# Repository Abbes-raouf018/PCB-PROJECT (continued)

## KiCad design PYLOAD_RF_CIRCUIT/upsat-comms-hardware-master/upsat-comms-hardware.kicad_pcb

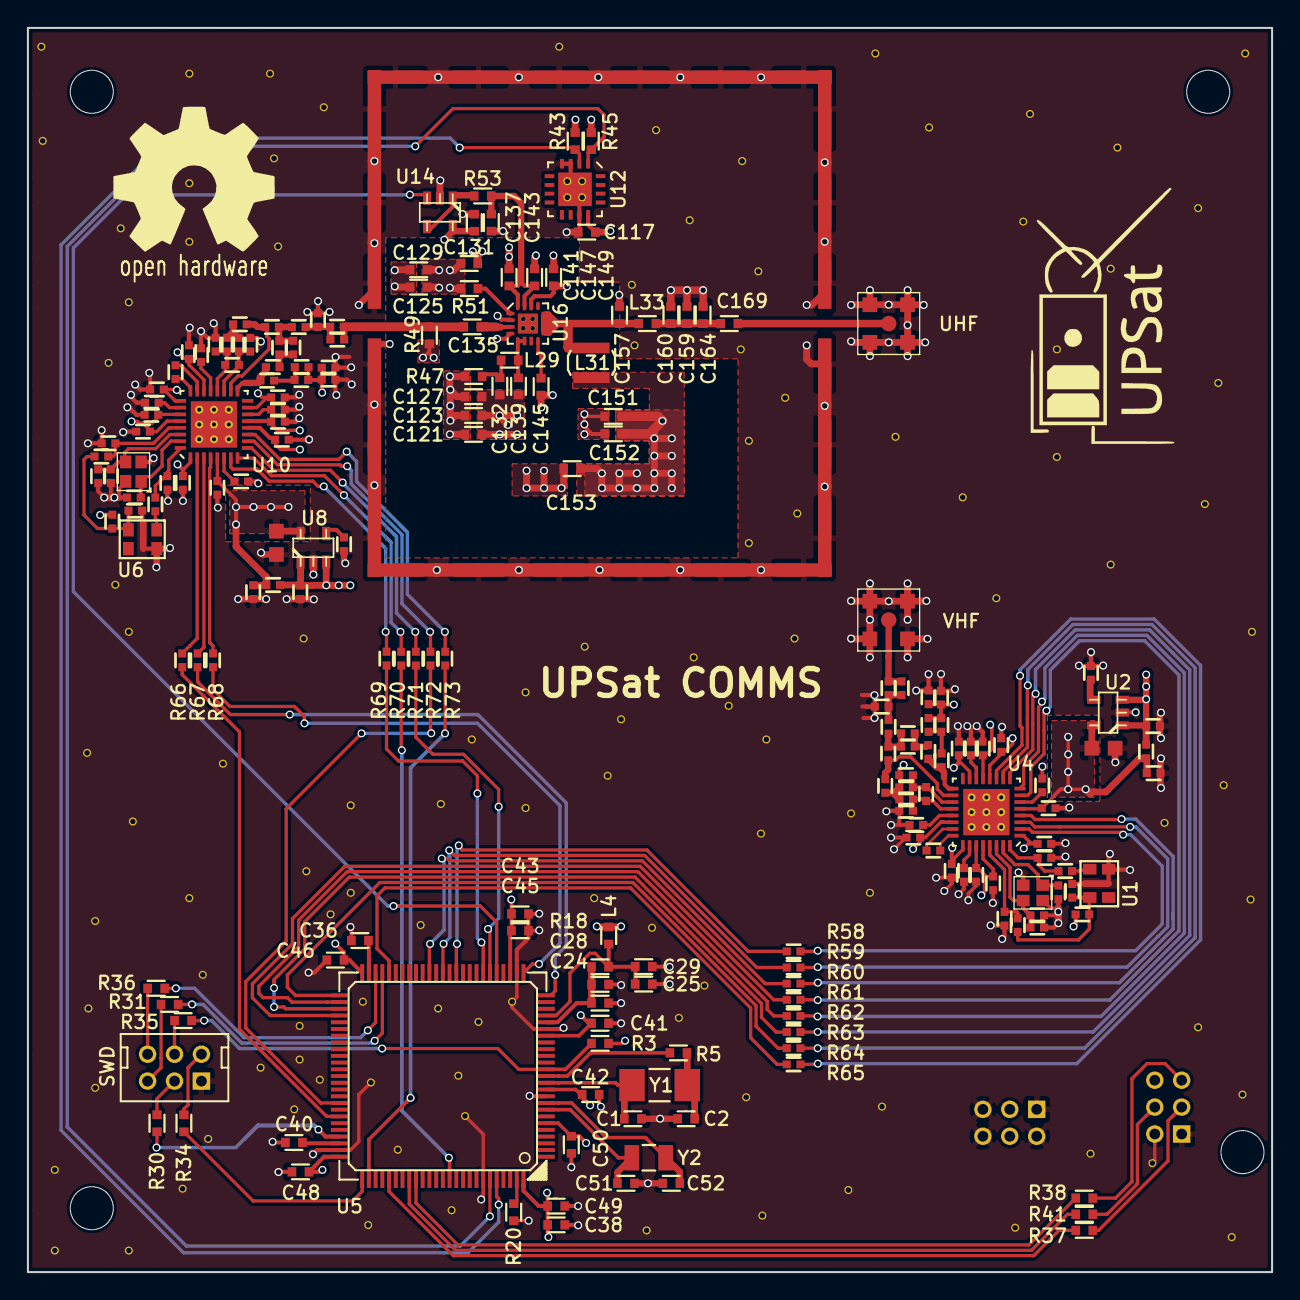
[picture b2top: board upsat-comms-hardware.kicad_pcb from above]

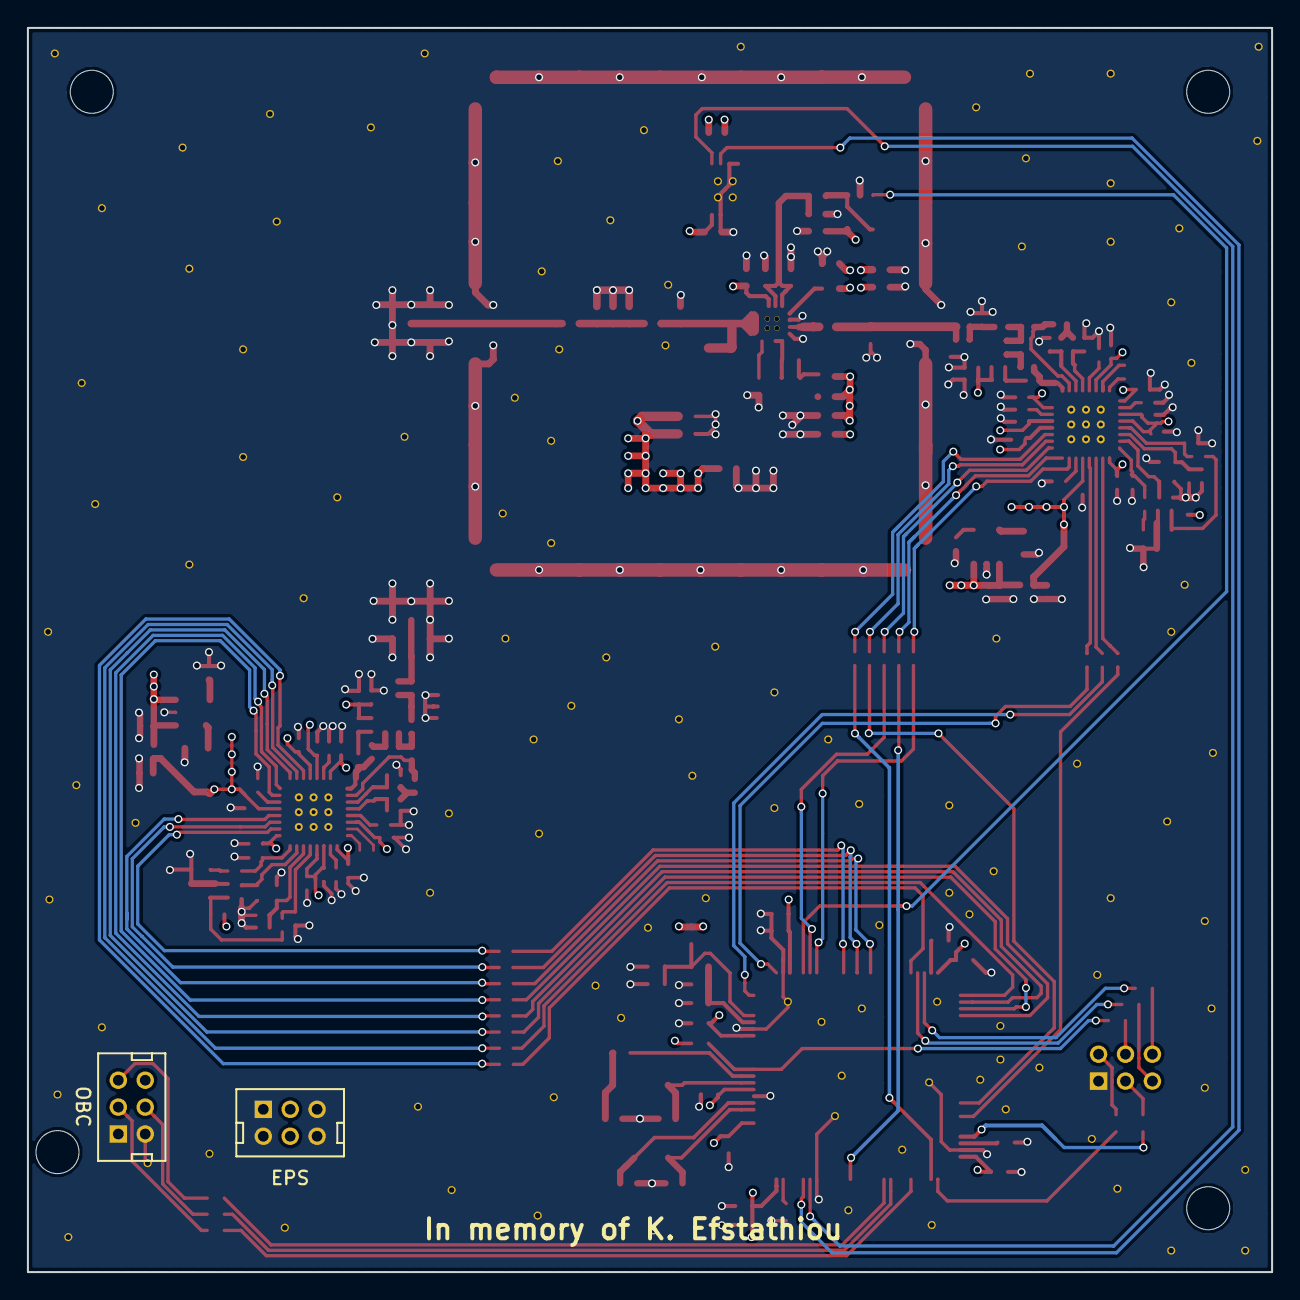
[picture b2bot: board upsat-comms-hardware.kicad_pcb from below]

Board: 4 copper layers, 92.5 x 92.5 mm, 195 parts (2 on the bottom side), 120 nets.

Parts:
C1, C2: 20pF; 0603murata2
C3, C4, C53, C55: 100nF; 0402_cc
C5, C6, C12, C13, C15, C16, C18, C19, C21, C22, C23, C26, C57, C58, C71, C73, C77, C79, C83, C85, C89, C91, C93, C95: 47nF; 0402_cc
C7, C61: 220nF; 0402_cc
C8, C27, C30, C62, C96, C99: 10nF; 0402_cc
C9, C65: 22pF; 0402_cc
C10, C11, C67, C69: 15pF; 0402_cc
C14, C75: TBD; 0402_cc
C17, C81: 2.2uF; CC1120DecCAP
C20, C87: 1.8nF; 0402_cc
C24, C25, C38, C41, C42, C43, C45, C46, C48, C49, C137: 100nF; 0603murata2
C28, C29, C50: 1uF; 0603murata2
C31: 150 pF; 0402_cc
C32: 100 pF; 0402_cc
C33, C105: 100pF; 0402_cc
C34, C35, C37, C39: 15 pF; 0402_cc
C36, C40: 2.2uF; 0603murata2
C44: 18 pF; 0402_cc
C47: 1.8 pF; 0402_cc
C51, C52: 6.8pF; 0603murata2
C101: 39pF; 0402_cc
C103: 56pF; 0402_cc
C107: 2.2pF; 0402_cc
C109, C111, C113: 5.1pF; 0402_cc
C115: 6.2pF; 0402_cc
C117: 0.1uF; 0603murata2
C118: do not mount; 0402_cc
C121, C153: 3.3uF; 0603murata2
C123, C125, C141, C147: 10000pF; 0603murata2
C127, C129, C143, C152: 1nF; 0603murata2
C131, C132: 330pF; 0603murata2
C135, C169: 56pF; 0603murata2
C139, C145: 18pF; 0603murata2
C149, C151: 47pF; 0603murata2
C157: TBD; 0603murata2
C159: 6.8 pF; 0603murata2
C160: 22 pF; 0603murata2
C164: 4 pF; 0603murata2
EPS: CONN_02X03; hrs-df11-6dp-2dsa
L1, L11: BLM15HG102SN1D; 0402_cc
L2: 150 nH; 0402_cc
L3: 180 nH; 0402_cc
L4: fcm1608-0603; 0603murata2
L5: 19 nH; 0402_cc
L6, L7: 91 nH; 0402_cc
L8: 120 nH; 0402_cc
L9: 43 nH; 0402_cc
L10: 75 nH; 0402_cc
L13, L15: 56nH; 0402_cc
L17, L25: 15nH; 0402_cc
L19, L21: 27nH; 0402_cc
L23: 43nH; 0402_cc
L27: 22nH; 0402_cc
L29: 6.8nH; 0603murata2
L31: Taiyo Yuden; Taiyo_Yuden_bead
L33: 4.3 nH; 0603murata2
OBC: OBC; hrs-df11-6dp-2dsa
R3, R43, R45: 10K; 0603murata2
R5: 220; 0603murata2
R8, R9, R10, R24, R26, R27, R58, R59, R60, R61, R62, R63, R64, R65, R66, R67, R68, R69, R70, R71, R72, R73: 0; 0402_cc
R17, R32: 56K; 0402_cc
R18: 47; 0603murata2
R19: 22 Ohm; 0402_cc
R20, R47: 0; 0603murata2
R30, R31, R34, R35, R36, R37, R38, R41: 470; 0603murata2
R39: 18; 0402_cc
R49: 180; 0603murata2
R51: 18; 0603murata2
R53: 180 Ohm; 0603murata2
RFSHIELD1: TEST_1P; BMI-S-x06
SWD: SWD; hrs-df11-6dp-2dsa
U1, U6: TXCO_TG_5021CG; TXCOTG5021CG
U2, U8: TPS79930; sot23-5
U3, U18: FA_128_; crystal_fa128
U4, U10: CC1120; cc1120
U5: STM32F407VG; TQFP-100
U12: ADT7420
U14: OPA320; sot23-5
U16: RF5110G
UHF: SMA; mmcx_conn
VHF: SMA; mmcx_conn
Y1: Crystal; ABM3crystal
Y2: Crystal; ABS07crystal

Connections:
+3V3: C4.1, C38.1, C41.1, C42.1, C43.1, C45.1, C46.1, C48.1, C49.1, C50.1, C55.1, C117.1, C121.1, C123.1, C125.1, C127.1, C129.1, C131.1, C137.1, C149.1, C151.2, C152.2, C153.2, EPS.3, EPS.4, L1.2, L4.2, L11.2, L31.2, R3.2, R43.1, R45.1, R47.1, R51.1, U2.1, U2.3, U5.6, U5.11, U5.19, U5.28, U5.50, U5.75, U5.100, U8.1, U8.3, U12.12, U14.5, U16.14
/1CS_N: R73.1, U5.77
/1GPIO0: R72.1, U5.67
/1GPIO2: R68.1, U5.26
/1GPIO3: R67.1, U5.25
/1RESET_N: R66.1, U5.69
/2CS_N: R65.1, U5.46
/2GPIO0: R64.1, U5.51
/2GPIO2: R60.1, U5.40
/2GPIO3: R59.1, U5.38
/2RESET_N: R58.1, U5.36
/COMMS_TO_OBC_EN: R38.2, U5.84
/COMMS_TO_OBC_RX: R41.1, U5.83
/COMMS_TO_OBC_TX: R37.2, U5.80
/DAC_OUT2: U5.30, U14.3
/I2C1_SCL: R45.2, U5.95, U12.1
/I2C1_SDA: R43.2, U5.96, U12.2
/NRST: R3.1, R35.1, U5.14
/SPI1_MISO: R71.1, U5.31
/SPI1_MOSI: R69.1, U5.32
/SPI1_SCK: R70.1, U5.89
/SPI2_MISO: R63.1, U5.53
/SPI2_MOSI: R61.1, U5.54
/SPI2_SCK: R62.1, U5.52
/SWCLK: R34.1, U5.76
/SWDIO: R30.2, U5.72
/USART3_RX: R36.1, U5.48
/USART3_TX: R31.2, U5.47
GND: C1.1, C2.1, C3.2, C4.2, C5.2, C6.2, C7.2, C8.2, C10.1, C11.1, C12.1, C13.2, C14.1, C15.2, C16.1, C17.2, C18.2, C19.1, C21.1, C22.2, C23.1, C24.2, C25.1, C26.1, C27.1, C28.2, C29.1, C30.2, C33.2, C35.1, C36.2, C38.2, C40.2, C41.2, C42.2, C43.2, C44.2, C45.2, C46.2, C48.2, C49.2, C50.2, C51.1, C52.1, C53.2, C55.2, C57.2, C58.2, C61.2, C62.2, C67.1, C69.1, C71.1, C73.2, C75.1, C77.2, C79.1, C81.2, C83.2, C85.1, C89.1, C91.2, C93.1, C95.1, C96.1, C99.2, C105.2, C109.1, C115.2, C117.2, C121.2, C123.2, C125.2, C127.2, C129.2, C131.2, C132.2, C137.2, C139.2, C141.2, C143.2, C145.2, C147.2, C149.2, C151.1, C152.1, C153.1, C157.1, C159.1, C160.2, C164.2, EPS.1, EPS.2, EPS.5, EPS.6, L7.1, L21.1, OBC.1, OBC.2, R10.1, R17.2, R20.2, R27.1, R32.2, R49.2, RFSHIELD1.1, SWD.1, U1.2, U2.2, U3.2, U3.4, U4.33, U5.10, U5.20, U5.27, U5.74, U5.94, U6.2, U8.2, U10.33, U12.3, U12.4, U12.11, U12.17, U14.2, U16.2, U16.4, U16.17, U18.2, U18.4, UHF.2, UHF.3, UHF.4, UHF.5, VHF.2, VHF.3, VHF.4, VHF.5
unnamed: C1.2, U5.12, Y1.1
unnamed: C2.2, R5.2, Y1.2
unnamed: C3.1, R8.2, R9.1, U1.4
unnamed: C7.1, U4.6
unnamed: C8.1, U2.4
unnamed: C9.1, R10.2, U4.32
unnamed: C9.2, U1.3
unnamed: C10.2, U3.1, U4.31
unnamed: C11.2, C14.2, U3.3, U4.30
unnamed: C12.2, R9.2, U4.29
unnamed: C20.1, U4.23
unnamed: C20.2, U4.24
unnamed: C21.2, U4.26
unnamed: C24.1, C28.1, R18.1, U5.21
unnamed: C25.2, C29.2, L4.1, R18.2, U5.22
unnamed: C27.2, U4.21
unnamed: C31.1, C34.2, L5.2
unnamed: C31.2, L2.1, U4.17
unnamed: C32.1, L2.2, R19.1
unnamed: C34.1, C39.2, L5.1, L8.2
unnamed: C35.2, L3.1, L6.2, U4.20
unnamed: C36.1, U5.49
unnamed: C37.1, L6.1, L9.1
unnamed: C37.2, L3.2, L7.2, U4.19
unnamed: C39.1, L9.2, U4.18
unnamed: C40.1, U5.73
unnamed: C44.1, C47.2, L8.1, L10.2
unnamed: C47.1, L10.1, VHF.1
unnamed: C51.2, U5.8, Y2.1
unnamed: C52.2, U5.9, Y2.2
unnamed: C53.1, R24.2, R26.1, U6.4
unnamed: C61.1, U10.6
unnamed: C62.1, U8.4
unnamed: C65.1, R27.2, U10.32
unnamed: C65.2, U6.3
unnamed: C67.2, U10.31, U18.1
unnamed: C69.2, C75.2, U10.30, U18.3
unnamed: C71.2, R26.2, U10.29
unnamed: C87.1, U10.23
unnamed: C87.2, U10.24
unnamed: C89.2, U10.26
unnamed: C96.2, U10.21
unnamed: C101.1, C107.2, L17.2
unnamed: C101.2, L13.1, U10.17
unnamed: C103.1, L13.2, R39.1
unnamed: C107.1, C113.2, L17.1, L23.2
unnamed: C109.2, L15.1, L19.2, U10.20
unnamed: C111.1, L19.1, L25.1
unnamed: C111.2, L15.2, L21.2, U10.19
unnamed: C113.1, L25.2, U10.18
unnamed: C115.1, C118.2, L23.1, L27.2
unnamed: C118.1, C135.2, L27.1, R49.1
unnamed: C132.1, L29.2, R47.2
unnamed: C135.1, U16.3
unnamed: C139.1, L29.1, U16.5, U16.6
unnamed: C141.1, C143.1, C147.1, R53.2, U16.15, U16.16
unnamed: C145.1, U16.8
unnamed: C157.2, L31.1, L33.2, U16.9, U16.10, U16.11, U16.12
unnamed: C159.2, C160.1, C164.1, C169.2, L33.1
unnamed: C169.1, UHF.1
unnamed: R34.2, SWD.2
unnamed: R30.1, SWD.3
unnamed: R35.2, SWD.4
unnamed: R31.1, SWD.5
unnamed: R36.2, SWD.6
unnamed: OBC.3, R37.1
unnamed: OBC.4, R41.2
unnamed: OBC.5, R38.1
unnamed: R5.1, U5.13
unnamed: R17.1, U4.14
unnamed: R20.1, U5.99
unnamed: R32.1, U10.14
unnamed: R51.2, U16.1
unnamed: R53.1, U14.1, U14.4
unnamed: R58.2, U4.2
unnamed: R59.2, U4.3
unnamed: R60.2, U4.4
unnamed: R61.2, U4.7
unnamed: R62.2, U4.8
unnamed: R63.2, U4.9
unnamed: R64.2, U4.10
unnamed: R65.2, U4.11
unnamed: R66.2, U10.2
unnamed: R67.2, U10.3
unnamed: R68.2, U10.4
unnamed: R69.2, U10.7
unnamed: R70.2, U10.8
unnamed: R71.2, U10.9
unnamed: R72.2, U10.10
unnamed: R73.2, U10.11
VDD: C5.1, C6.1, C13.1, C15.1, C16.2, C17.1, C18.1, C19.2, C22.1, C23.2, C26.2, C30.1, C32.2, C33.1, C57.1, C58.1, C73.1, C77.1, C79.2, C81.1, C83.1, C85.2, C91.1, C93.2, C95.2, C99.1, C103.2, C105.1, L1.1, L11.1, R8.1, R19.2, R24.1, R39.2, U2.5, U4.1, U4.5, U4.12, U4.13, U4.15, U4.22, U4.25, U4.27, U4.28, U8.5, U10.1, U10.5, U10.12, U10.13, U10.15, U10.22, U10.25, U10.27, U10.28

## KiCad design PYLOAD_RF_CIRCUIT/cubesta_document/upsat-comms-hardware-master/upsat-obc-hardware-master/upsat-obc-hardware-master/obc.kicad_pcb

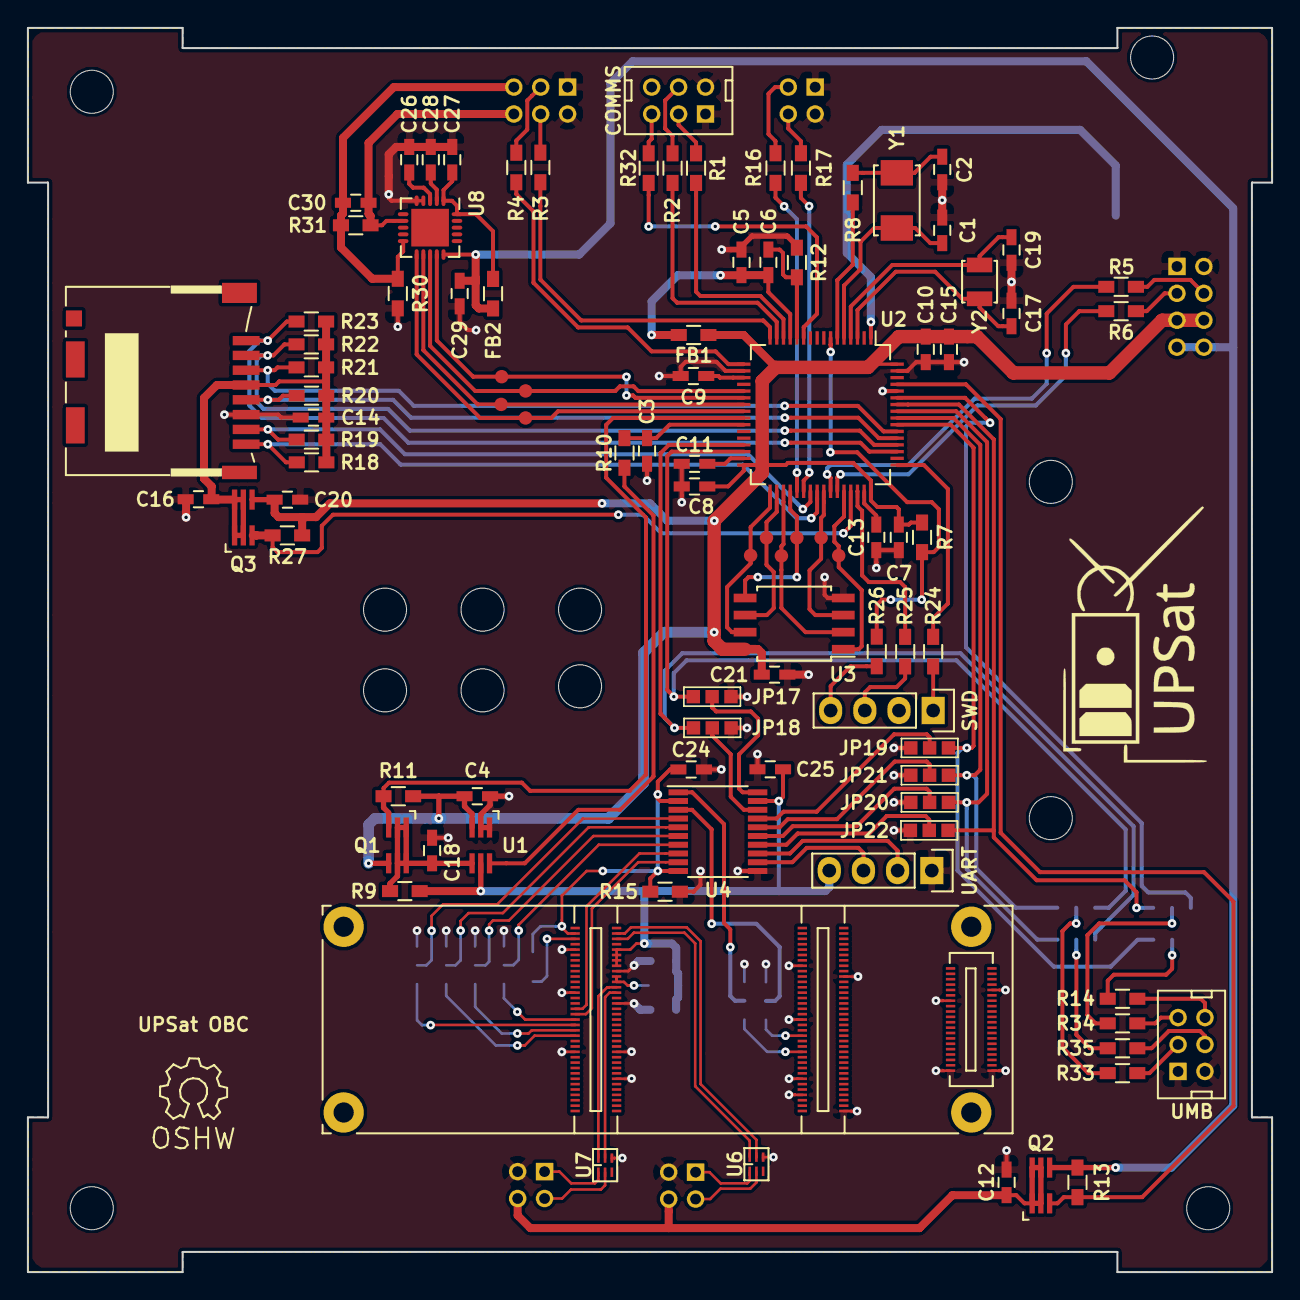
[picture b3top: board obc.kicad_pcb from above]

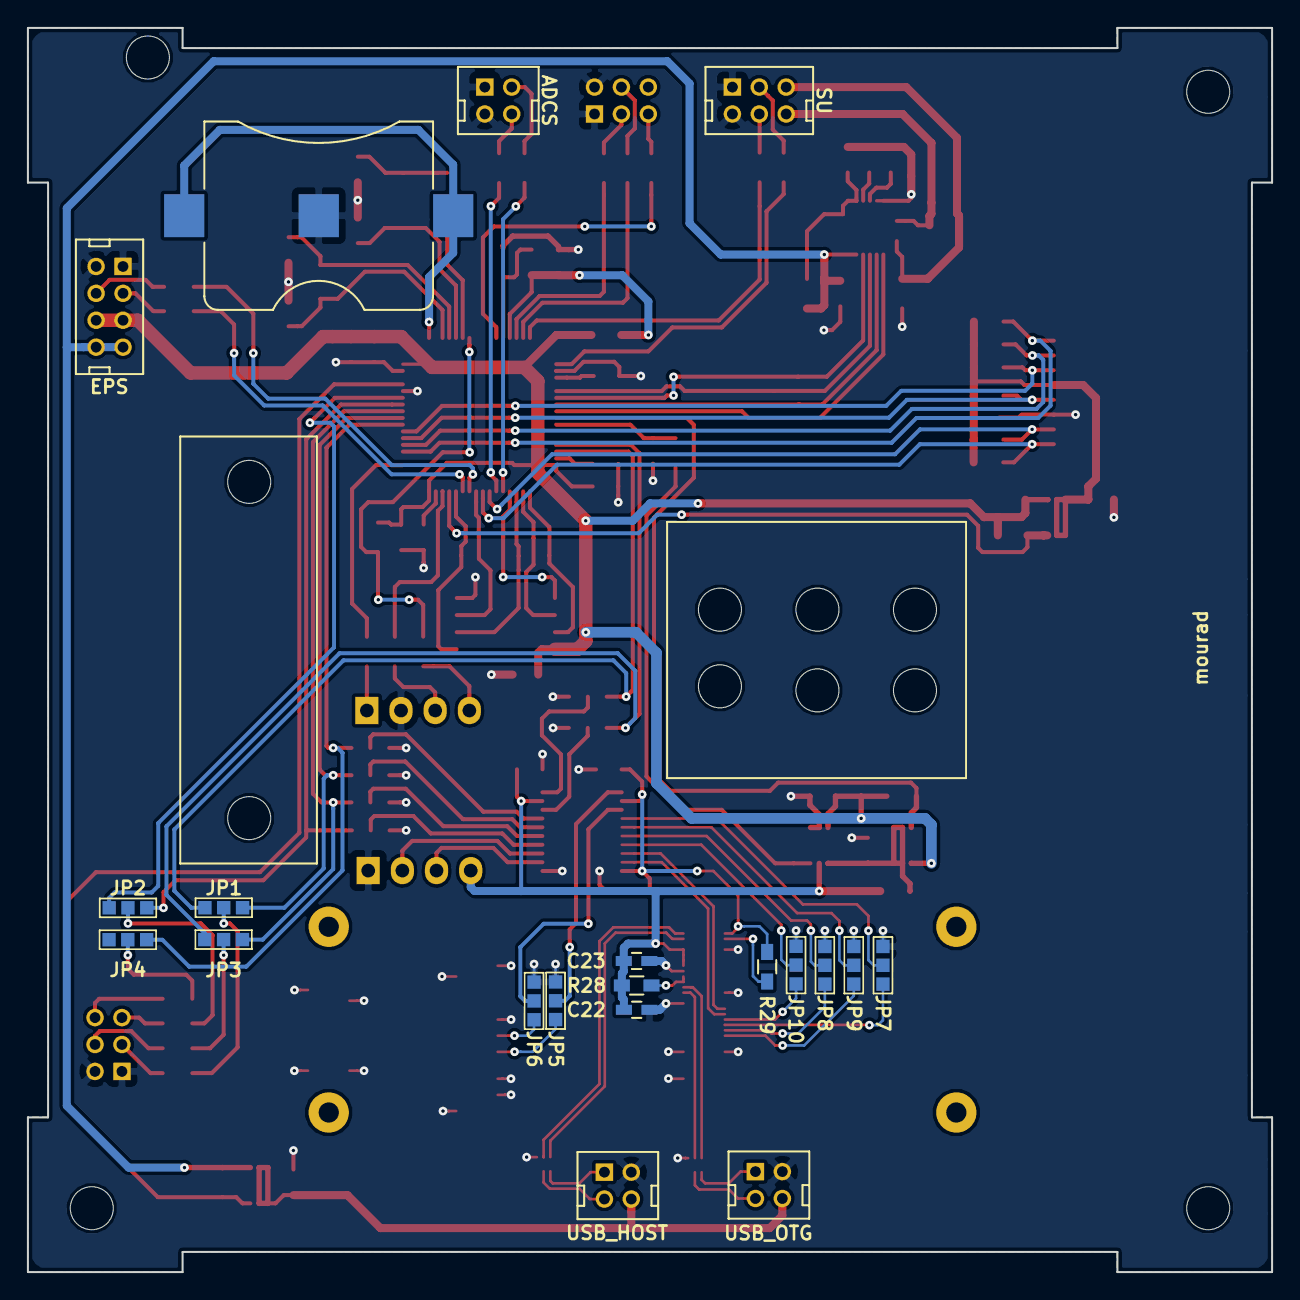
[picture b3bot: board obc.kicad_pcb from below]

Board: 2 copper layers, 92.5 x 92.5 mm, 119 parts (21 on the bottom side), 116 nets.

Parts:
BT1: Battery; renata-smtm1632
C1, C2: 20p; C_0603_HandSoldering
C3, C4, C7, C9, C10, C14, C20, C24, C25, C26, C30: 100n; C_0603_HandSoldering
C5, C11, C13, C27, C29: 2.2u; C_0603_HandSoldering
C6: 10n; C_0603_HandSoldering
C8, C12, C15, C16, C18, C21, C28: 10u; C_0603_HandSoldering
C17, C19: 6.8p; C_0603_HandSoldering
C22, C23: 22u; C_0603_HandSoldering
CAMERA1: upsat_camera
CON1: hrs-dm3cs
FB1, FB2: BLM18AG331SN1; R_0603_HandSoldering
JP1, JP2, JP3, JP4, JP5, JP6, JP7, JP8, JP9, JP10, JP17, JP18, JP19, JP20, JP21, JP22: JUMPER3; 3-way_bridge_0603
P1: EPS; hrs-df11-8dp-2dsa
P2: COMMS; hrs-df11-6dp-2dsa
P3: ADCS; hrs-df11-4dp-2dsa
P4: SU; hrs-df11-6dp-2dsa
P5: UMB; hrs-df11-6dp-2dsa
P6: SWD; Pin_Header_Straight_1x04
P7: UART; Pin_Header_Straight_1x04
P8: USB_HOST; hrs-df11-4dp-2dsa
P9: USB_OTG; hrs-df11-4dp-2dsa
Q1, Q2, Q3: Si1401EDH; SC-70-6_Handsoldering
R1, R2, R3, R4, R5, R6, R10, R14, R16, R17, R24, R25, R26, R32, R33, R34, R35: 470; R_0603_HandSoldering
R7: 10k; R_0603_HandSoldering
R8: 220; R_0603_HandSoldering
R9: 0.02; R_0603_HandSoldering
R11, R13, R27, R29: 100k; R_0603_HandSoldering
R12, R30: 0; R_0603_HandSoldering
R15, R28: 1k; R_0603_HandSoldering
R18, R19, R20, R21, R22, R23: 47k; R_0603_HandSoldering
R31: 2.4k; R_0603_HandSoldering
U1: INA214; SC-70-6_Handsoldering
U2: STM32F405R; LQFP-64_10x10mm_Pitch0.5mm
U3: IS25LP128; SOIJ-8_5.3x5.3mm_Pitch1.27mm
U4: TXB0108PWR; TSSOP-20_4.4x6.5mm_Pitch0.65mm
U5: DART-4460; dart-4460
U6, U7: ECMF02-3HSM6
U8: AD7689; UQFN-20-1EP_4x4mm_Pitch0.5mm
UPSat OBC: Symbol_OSHW-Logo_SilkScreen
W1, W2, W3, W4, W5, W6, W7, W8, W9, W10: TEST_1P; Measurement_Point_Round-SMD-Pad_Small
Y1: 12MHz; ABM3
Y2: 32.768kHz; ABS07crystal

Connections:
+3V3: C4.2, C7.1, C8.1, C10.1, C15.2, C20.1, C21.1, FB1.1, P1.5, P1.6, Q1.4, Q3.4, R7.2, R11.2, R27.2, U1.3, U2.32, U2.48, U2.64, U3.8
+5V: C29.1, FB2.2, P1.7, P1.8, Q2.4, R13.2, U8.15
/ADCS_RX: P3.4, R17.1
/ADCS_TX: P3.3, R16.1
/COMMS_EN: P2.5, R32.1
/COMMS_RX: P2.4, R2.1
/COMMS_TX: P2.3, R1.1
/EPS_RX: P1.3, R6.2
/EPS_TX: P1.4, R5.2
/F_CE: U2.44, U3.1, W3.1
/F_HOLD: U2.33, U3.7, W4.1
/F_MISO: U2.35, U3.2, W2.1
/F_MOSI: U2.36, U3.5, W6.1
/F_SCK: U2.34, U3.6, W5.1
/F_WP: U2.41, U3.3, W1.1
/IAC/+3.3V: C22.1, C23.1, C25.1, P7.4, R9.1, R28.2, U1.5, U4.19, U5.10, U5.12, U5.14, U5.16
/IAC/+5V: C12.2, P8.4, P9.4, Q2.1, Q2.2, Q2.5, Q2.6
/IAC/A1: JP5.2, U4.1
/IAC/A2: JP6.2, U4.3
/IAC/A5: JP7.2, U4.4
/IAC/A6: JP9.2, U4.5
/IAC/A7: JP8.2, U4.6
/IAC/A8: JP10.2, U4.7
/IAC/B1: JP17.2, U4.20
/IAC/B2: JP18.2, U4.18
/IAC/B5: JP19.2, U4.17
/IAC/B6: JP21.2, U4.16
/IAC/B7: JP20.2, U4.15
/IAC/B8: JP22.2, U4.14
/IAC/DART_CLK: JP7.1, U5.37
/IAC/DART_CS: JP10.1, U5.35
/IAC/DART_MISO: JP9.1, U5.41
/IAC/DART_MOSI: JP8.1, U5.39
/IAC/Dcon+: P8.1, U6.1
/IAC/Dcon-: P8.2, U6.2
/IAC/RX: JP3.3, JP18.3, U2.29
/IAC/RX1: JP6.1, U5.111
/IAC/RX3: U4.8, U5.31
/IAC/RX_UART: P7.2, U4.13
/IAC/TX: JP1.1, JP17.3, U2.30
/IAC/TX1: JP5.1, U5.117
/IAC/TX3: U4.9, U5.33
/IAC/TX_UART: P7.3, U4.12
/IAC/USB_HOST_D+: U5.6, U6.6
/IAC/USB_HOST_D-: U5.4, U6.5
/IAC/USB_OTG_D+: U5.24, U7.6
/IAC/USB_OTG_D-: U5.26, U7.5
/IAC/VIO: C24.1, R15.1, R29.1, U4.2, U4.10, U5.3
/IAC/uC_CS: JP2.1, JP22.3, U2.58
/IAC/uC_MISO: JP1.3, JP21.3, U2.56
/IAC/uC_MOSI: JP3.1, JP20.3, U2.57
/IAC/uC_SCK: JP4.3, JP19.3, U2.55
/IAC_CM: C3.2, R10.2, U2.26
/IAC_EN: Q1.3, R11.1, U2.25
/NRST: R7.1, R26.2, U2.7
/PC3: R32.2, U2.11
/SD1_3V3: C14.1, C16.1, CON1.4, Q3.1, Q3.2, Q3.5, Q3.6, R18.2, R19.2, R20.2, R21.2, R22.2, R23.2
/SD1_EN: Q3.3, R27.1, U2.45
/SDIO_CK: CON1.5, R20.1, U2.53
/SDIO_CMD: CON1.3, R21.1, U2.54
/SDIO_D0: CON1.7, R19.1, U2.39
/SDIO_D1: CON1.8, R18.1, U2.40
/SDIO_D2: CON1.1, R23.1, U2.51
/SDIO_D3: CON1.2, R22.1, U2.52
/SU/CNV: U2.24, U8.11, W10.1
/SU/DIN: U2.23, U8.12, W9.1
/SU/SCK: U2.21, U8.13, W8.1
/SU/SDO: U2.22, U8.14, W7.1
/SU/SU_TH_GO: C30.2, P4.5, R30.1, R31.2, U8.10
/SU/SU_TH_RET: C30.1, P4.6, R31.1, U8.7
/SU_RX: P4.3, R4.2
/SU_TX: P4.4, R3.2
/SWCLK: R24.2, U2.49
/SWDIO: R25.2, U2.46
/UART4_RX: R2.2, U2.15
/UART4_TX: R1.2, U2.14
/UMB_EN: JP2.3, U2.59
/USART1_RX: R6.1, U2.43
/USART1_TX: R5.1, U2.42
/USART2_RX: R4.1, U2.17
/USART2_TX: R3.1, U2.16
/USART6_RX: R17.2, U2.38
/USART6_TX: R16.2, U2.37
/USB_EN: Q2.3, R13.1, U2.61
GND: BT1.2, C1.1, C2.1, C3.1, C4.1, C5.2, C7.2, C8.2, C9.1, C10.2, C11.1, C12.1, C13.1, C14.2, C15.1, C16.2, C17.2, C18.1, C19.1, C20.2, C21.2, C22.2, C23.2, C24.2, C25.2, C26.2, C27.2, C28.2, C29.2, CON1.6, JP5.3, JP6.3, JP7.3, JP8.3, JP9.3, JP10.3, JP17.1, JP18.1, JP19.1, JP20.1, JP21.1, JP22.1, P1.1, P1.2, P2.1, P2.2, P3.1, P3.2, P4.1, P4.2, P5.1, P5.2, P6.2, P7.1, P8.3, P9.3, R12.2, R15.2, R30.2, U1.1, U1.2, U2.18, U2.60, U2.63, U3.4, U4.11, U5.9, U5.18, U5.25, U5.30, U5.47, U5.48, U5.58, U5.85, U5.90, U5.105, U5.127, U5.133, U5.140, U5.150, U5.153, U5.179, U5.180, U6.4, U7.4, U8.4, U8.5
GNDA: C6.2, R12.1, U2.12
unnamed: BT1.1, U2.1
unnamed: C1.2, U2.5, Y1.2
unnamed: C2.2, R8.2, Y1.1
unnamed: C5.1, C6.1, FB1.2, U2.13
unnamed: C9.2, U2.19
unnamed: C11.2, U2.31
unnamed: C13.2, U2.47
unnamed: C17.1, U2.3, Y2.2
unnamed: C18.2, Q1.1, Q1.2, Q1.5, Q1.6, R9.2, U1.4
unnamed: C19.2, U2.4, Y2.1
unnamed: C26.1, U8.3
unnamed: C27.1, FB2.1, U8.1, U8.20
unnamed: C28.1, U8.2
unnamed: JP1.2, R33.1
unnamed: JP2.2, R34.2
unnamed: JP3.2, R35.2
unnamed: JP4.2, R14.1
unnamed: P5.3, R33.2
unnamed: P5.4, R35.1
unnamed: P5.5, R34.1
unnamed: P5.6, R14.2
unnamed: P6.1, R24.1
unnamed: P6.3, R25.1
unnamed: P6.4, R26.1
unnamed: P9.1, U7.1
unnamed: P9.2, U7.2
unnamed: R8.1, U2.6
unnamed: R10.1, U1.6
unnamed: R28.1, U5.20, U5.22
unnamed: R29.2, U5.5

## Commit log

2024-02-24 ok test
2024-02-24 ok endo watch ready for manufacturing
2024-02-24 design board to control stpper and brushless motor
2024-02-24 lithium charge battery one cell with protection
2024-02-24 Design board stm32F103
2024-02-24 Mini SMPS
2024-02-24 design circuit RF for CUBE CUBE AMAIN BOARD
2024-02-24 Design board IN PROGRESS
2024-02-25 rmc pcb inprogress
2024-03-24 XW-AC230 power supply
2024-03-24 GPS tracker mini project
